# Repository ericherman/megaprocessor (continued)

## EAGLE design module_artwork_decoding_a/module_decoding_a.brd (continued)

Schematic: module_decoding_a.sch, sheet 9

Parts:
CMP98: 2AND
CMP104: 3OR

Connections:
END_OF_SHIFT: CMP98.OUT_P; also elsewhere on the board
OPCODE_IS_ANDI_ORI_PS_LDI_X: CMP104.OUT_P; also elsewhere on the board
OPCODE_IS_ANDI_PS: CMP104.P$2 (1); also elsewhere on the board
OPCODE_IS_LDI_X: CMP104.P$1 (0); also elsewhere on the board
OPCODE_IS_ORI_PS: CMP104.P$3 (2); also elsewhere on the board
OPCODE_IS_SHIFT_XX: CMP98.P$2 (2); also elsewhere on the board
SHIFT_VAL_NON_ZERO_N: CMP98.P$1 (1); also elsewhere on the board

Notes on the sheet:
end_of_shift= Cpnt_2AND(opcode_is_shift_xx, ~shift_val_non_zero);
opcode_is_andi_ori_ps_ldi_x = Cpnt_3OR(opcode_is_ldi_x, opcode_is_andi_ps, opcode_is_ori_ps);

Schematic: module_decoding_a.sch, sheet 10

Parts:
CMP40, CMP43: 3OR
CMP44, CMP45: 2X2AND_OR

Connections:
DIV_BY_ZERO: CMP40.P$3 (2); also elsewhere on the board
DOING_EXCEPTION: CMP43.OUT_P
DOING_EXCEPTION_N: CMP43.OUT_M (N), CMP44.P$3 (B0), CMP44.P$4 (B1), CMP45.P$3 (B0), CMP45.P$4 (B1)
FLAG_F4: CMP43.P$2 (1), CMP44.P$2 (A1); also elsewhere on the board
FLAG_F5: CMP43.P$1 (0), CMP45.P$1 (A0); also elsewhere on the board
RESET_SIGNAL: CMP40.P$1 (0), CMP43.P$3 (2); also elsewhere on the board
RESET_SIGNAL_N: CMP44.P$1 (A0), CMP45.P$2 (A1); also elsewhere on the board
TAKE_EXCEPTION: CMP40.OUT_P; also elsewhere on the board
TAKE_INTERRUPT: CMP40.P$2 (1); also elsewhere on the board
VECTOR_CODE_0: CMP44.OUT_P; also elsewhere on the board
VECTOR_CODE_1: CMP45.OUT_P; also elsewhere on the board

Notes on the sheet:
take_exception = Cpnt_3OR(div_by_zero , take_interrupt, reset_signal);
opcode_is_div_state_0 = Cpnt_2AND(opcode_is_div, bus_state[0]);
doing_exception = Cpnt_3OR(bus_PS[WiC_PS_FLAG_INDEX_F4], bus_PS[WiC_PS_FLAG_INDEX_F5],reset_signal);
vector_code_0 = Cpnt_2x2AND_OR(~doing_exception, ~doing_exception, bus_PS[WiC_PS_FLAG_INDEX_F4], ~reset_signal);
vector_code_1 = Cpnt_2x2AND_OR(~doing_exception, ~doing_exception, bus_PS[WiC_PS_FLAG_INDEX_F5], ~reset_signal);

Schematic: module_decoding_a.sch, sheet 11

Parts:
CMP4, CMP46: 1BUF

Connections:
FLAG_F2: CMP46.IN; also elsewhere on the board
FLAG_F2_BUF: CMP46.P; also elsewhere on the board
FLAG_F2_N: CMP46.N; also elsewhere on the board
RESET_SIGNAL: CMP4.IN; also elsewhere on the board
RESET_SIGNAL_N: CMP4.N; also elsewhere on the board

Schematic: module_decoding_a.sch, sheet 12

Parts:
CMP58, CMP81: BUS_CONSTRUCT_DISPLAY; BUS_SPLIT_DISPLAY

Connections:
BUS_DECODE_SPECIAL_REG_0: CMP81.INPUT (OUT)
BUS_DECODE_SPECIAL_REG_1: CMP58.INPUT (OUT)
FLAG_F2_N: CMP58.P$3 (IN_2); also elsewhere on the board
INSTR_2: CMP81.P$2 (IN_1); also elsewhere on the board
IS_END: CMP58.P$9 (IN_8); also elsewhere on the board
IS_NOT_INTERRUPTING_END: CMP58.P$16 (IN_15); also elsewhere on the board
OPCODE_IS_ABSOLUTE_GROUP: CMP81.P$12 (IN_11); also elsewhere on the board
OPCODE_IS_ADD_SP: CMP58.P$7 (IN_6); also elsewhere on the board
OPCODE_IS_ANDI_ORI_PS_LDI_X: CMP58.P$8 (IN_7); also elsewhere on the board
OPCODE_IS_BRANCH_GROUP: CMP58.P$6 (IN_5); also elsewhere on the board
OPCODE_IS_BXX_STATE_2: CMP58.P$12 (IN_11); also elsewhere on the board
OPCODE_IS_INDIRECT_POSTINC: CMP81.P$3 (IN_2); also elsewhere on the board
OPCODE_IS_JMP_ABS: CMP58.P$10 (IN_9); also elsewhere on the board
OPCODE_IS_JMP_R0: CMP58.P$5 (IN_4); also elsewhere on the board
OPCODE_IS_JSR_ABS: CMP81.P$6 (IN_5); also elsewhere on the board
OPCODE_IS_JSR_R0: CMP81.P$5 (IN_4); also elsewhere on the board
OPCODE_IS_JSR_X_STATE_7: CMP58.P$4 (IN_3); also elsewhere on the board
OPCODE_IS_MOVE_SP_R0: CMP58.P$2 (IN_1); also elsewhere on the board
OPCODE_IS_MUL_SQRT_DIV: CMP58.P$15 (IN_14); also elsewhere on the board
OPCODE_IS_POP_RA_PS: CMP81.P$14 (IN_13); also elsewhere on the board
OPCODE_IS_PUSH_PS: CMP81.P$9 (IN_8); also elsewhere on the board
OPCODE_IS_PUSH_RA: CMP81.P$1 (IN_0); also elsewhere on the board
OPCODE_IS_RET_RETI: CMP58.P$11 (IN_10); also elsewhere on the board
OPCODE_IS_SHIFT_BIT: CMP81.P$10 (IN_9); also elsewhere on the board
OPCODE_IS_SHIFT_XX: CMP81.P$16 (IN_15); also elsewhere on the board
OPCODE_IS_STACK_GROUP: CMP58.P$1 (IN_0); also elsewhere on the board
OPCODE_IS_STACK_REL_GROUP: CMP81.P$11 (IN_10); also elsewhere on the board
OPCODE_IS_STACK_REL_STATE_2: CMP81.P$15 (IN_14); also elsewhere on the board
OPCODE_IS_TRAP: CMP81.P$8 (IN_7); also elsewhere on the board
TAKE_EXCEPTION: CMP81.P$13 (IN_12); also elsewhere on the board
VECTOR_CODE_0: CMP58.P$13 (IN_12); also elsewhere on the board
VECTOR_CODE_1: CMP58.P$14 (IN_13); also elsewhere on the board
WILL_BE_STATE_6: CMP81.P$7 (IN_6); also elsewhere on the board
WILL_BE_STATE_7: CMP81.P$4 (IN_3); also elsewhere on the board

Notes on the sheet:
clBit opcode_is_push_ra; // 0 clBit size_bit_is_byte; // 1 clBit opcode_is_indirect_postinc; // 2 clBit will_be_7; // 3 clBit opcode_is_jsr_r0; // 4 clBit opcode_is_jsr_abs; // 5 clBit will_be_6; // 6 clBit opcode_is_trap; // 7 clBit opcode_is_push_ps; // 8 clBit opcode_is_shift_bit; // 9 clBit opc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
clBit opcode_is_stack_group; // 0 clBit opcode_is_move_sp_r0; // 1 clBit flag_F2_n; // 2 clBit opcode_is_jsr_x_state_7; // 3 clBit opcode_is_jmp_r0; // 4 clBit opcode_is_bxx; // 5 clBit opcode_is_add_sp; // 6 clBit opcode_is_andi_ori_ps_ldi_x; // 7 clBit is_end; // 8 clBit opcode_is_jmp_abs; // 9 c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

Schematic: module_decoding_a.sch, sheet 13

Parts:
CMP83, CMP85, CMP89: BUS_CONSTRUCT_DISPLAY; BUS_SPLIT_DISPLAY

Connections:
BRANCH_NOT_TAKEN: CMP85.P$3 (IN_2); also elsewhere on the board
BRANCH_TAKEN: CMP83.P$10 (IN_9); also elsewhere on the board
BUS_DECODE_STATE_1: CMP83.INPUT (OUT)
BUS_DECODE_STATE_2: CMP85.INPUT (OUT)
BUS_DECODE_STATE_3: CMP89.INPUT (OUT)
DIR_SZ_IS_LOAD_BYTE: CMP85.P$12 (IN_11); also elsewhere on the board
DIR_SZ_IS_LOAD_WORD: CMP85.P$9 (IN_8); also elsewhere on the board
DIV_BY_ZERO: CMP83.P$1 (IN_0); also elsewhere on the board
END_OF_SHIFT: CMP85.P$6 (IN_5); also elsewhere on the board
FLAG_F2_BUF: CMP85.P$1 (IN_0); also elsewhere on the board
H_COUNT_IS_15: CMP83.P$16 (IN_15); also elsewhere on the board
INSTR_0: CMP89.P$3 (IN_2); also elsewhere on the board
IS_END: CMP83.P$2 (IN_1); also elsewhere on the board
LDI_X_STATE_0_BYTE_1_WORD: CMP83.P$13 (IN_12); also elsewhere on the board
unnamed: CMP89.P$6 (IN_5), CMP89.P$7 (IN_6), CMP89.P$8 (IN_7), CMP89.P$9 (IN_8), CMP89.P$10 (IN_9), CMP89.P$11 (IN_10), CMP89.P$12 (IN_11), CMP89.P$13 (IN_12), CMP89.P$14 (IN_13), CMP89.P$15 (IN_14), CMP89.P$16 (IN_15)
OPCODE_IS_ABSOLUTE_GROUP: CMP83.P$6 (IN_5); also elsewhere on the board
OPCODE_IS_ADD_SP: CMP83.P$11 (IN_10); also elsewhere on the board
OPCODE_IS_ADD_SP_STATE_2: CMP83.P$14 (IN_13); also elsewhere on the board
OPCODE_IS_ANDI_ORI_PS: CMP85.P$4 (IN_3); also elsewhere on the board
OPCODE_IS_BIT_XX: CMP83.P$4 (IN_3); also elsewhere on the board
OPCODE_IS_BRANCH_GROUP: CMP85.P$7 (IN_6); also elsewhere on the board
OPCODE_IS_DIV_STATE_0: CMP89.P$2 (IN_1); also elsewhere on the board
OPCODE_IS_JMP_ABS: CMP83.P$5 (IN_4); also elsewhere on the board
OPCODE_IS_JMP_R0: CMP85.P$2 (IN_1); also elsewhere on the board
OPCODE_IS_JSR_ABS: CMP83.P$7 (IN_6); also elsewhere on the board
OPCODE_IS_JSR_X_STATE_7: CMP83.P$15 (IN_14); also elsewhere on the board
OPCODE_IS_MOVER_SP: CMP85.P$5 (IN_4); also elsewhere on the board
OPCODE_IS_MUL: CMP89.P$4 (IN_3); also elsewhere on the board
OPCODE_IS_RET: CMP85.P$11 (IN_10); also elsewhere on the board
OPCODE_IS_RETI: CMP85.P$15 (IN_14); also elsewhere on the board
OPCODE_IS_SHIFT_XX: CMP83.P$3 (IN_2); also elsewhere on the board
OPCODE_IS_SQRT: CMP89.P$1 (IN_0); also elsewhere on the board
OPCODE_IS_STACK_REL_GROUP: CMP83.P$9 (IN_8); also elsewhere on the board
OPCODE_IS_TRAP: CMP89.P$5 (IN_4); also elsewhere on the board
SHIFT_IS_SHIFTING: CMP83.P$12 (IN_11); also elsewhere on the board
START_TRANSFER_CYCLE: CMP85.P$10 (IN_9); also elsewhere on the board
TRAP_STATE_7: CMP85.P$16 (IN_15); also elsewhere on the board
UNSIGNED_15: CMP85.P$8 (IN_7); also elsewhere on the board
WILL_BE_1__LDI: CMP83.P$8 (IN_7); also elsewhere on the board
WILL_BE_STATE_6: CMP85.P$13 (IN_12); also elsewhere on the board
WILL_BE_STATE_7: CMP85.P$14 (IN_13); also elsewhere on the board

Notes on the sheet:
clBit opcode_is_sqrt; // 0 clBit opcode_is_div_state_0; // 1 clBit type_bit_is_signed; // 2 clBit opcode_is_mul; // 3 clBit opcode_is_trap; // 4
clBit reset_flag; // 0 clBit opcode_is_jmp_r0; // 1 clBit branch_not_taken; // 2 clBit opcode_is_andi_ori_ps; // 3 clBit opcode_is_mover_sp; // 4 clBit end_of_shift; // 5 clBit opcode_is_branch_group; // 6 clBit unsigned_15; // 7 clBit dir_sz_is_load_word; // 8 clBit start_transfer_cycle; // 9 clBi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
clBit div_by_zero; // 0 clBit is_end; // 1 clBit opcode_is_shift_xx; // 2 clBit opcode_is_bit_xx; // 3 clBit opcode_is_jmp_abs; // 4 clBit opcode_is_absolute_group; // 5 clBit opcode_is_jsr_abs; // 6 clBit will_be_1__ldi; // 7 clBit opcode_is_stack_rel_group; // 8 clBit branch_taken; // 9 clBit opc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

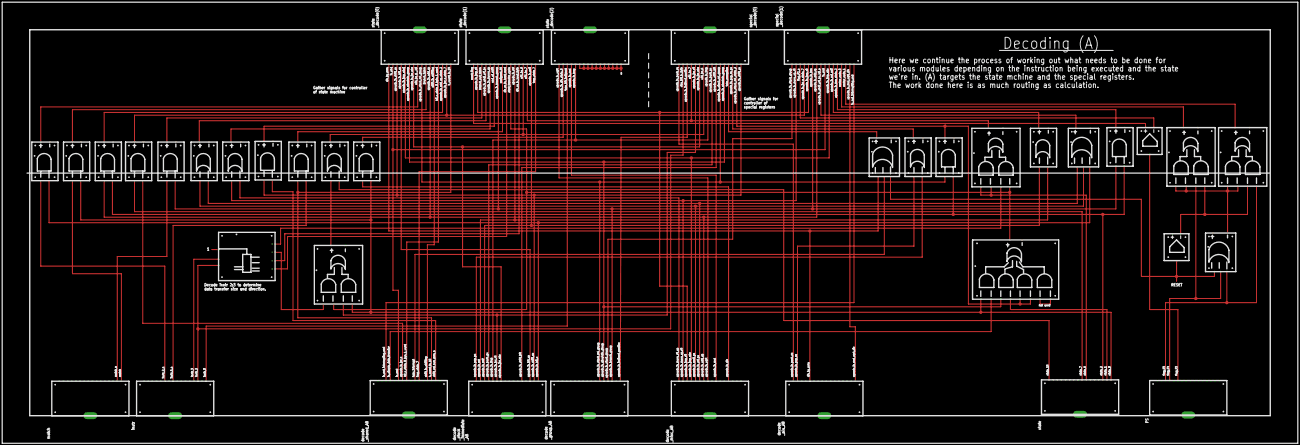
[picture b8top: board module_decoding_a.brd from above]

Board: 2 copper layers, 1193.8 x 406.4 mm, 40 parts (0 on the bottom side), 89 nets.
